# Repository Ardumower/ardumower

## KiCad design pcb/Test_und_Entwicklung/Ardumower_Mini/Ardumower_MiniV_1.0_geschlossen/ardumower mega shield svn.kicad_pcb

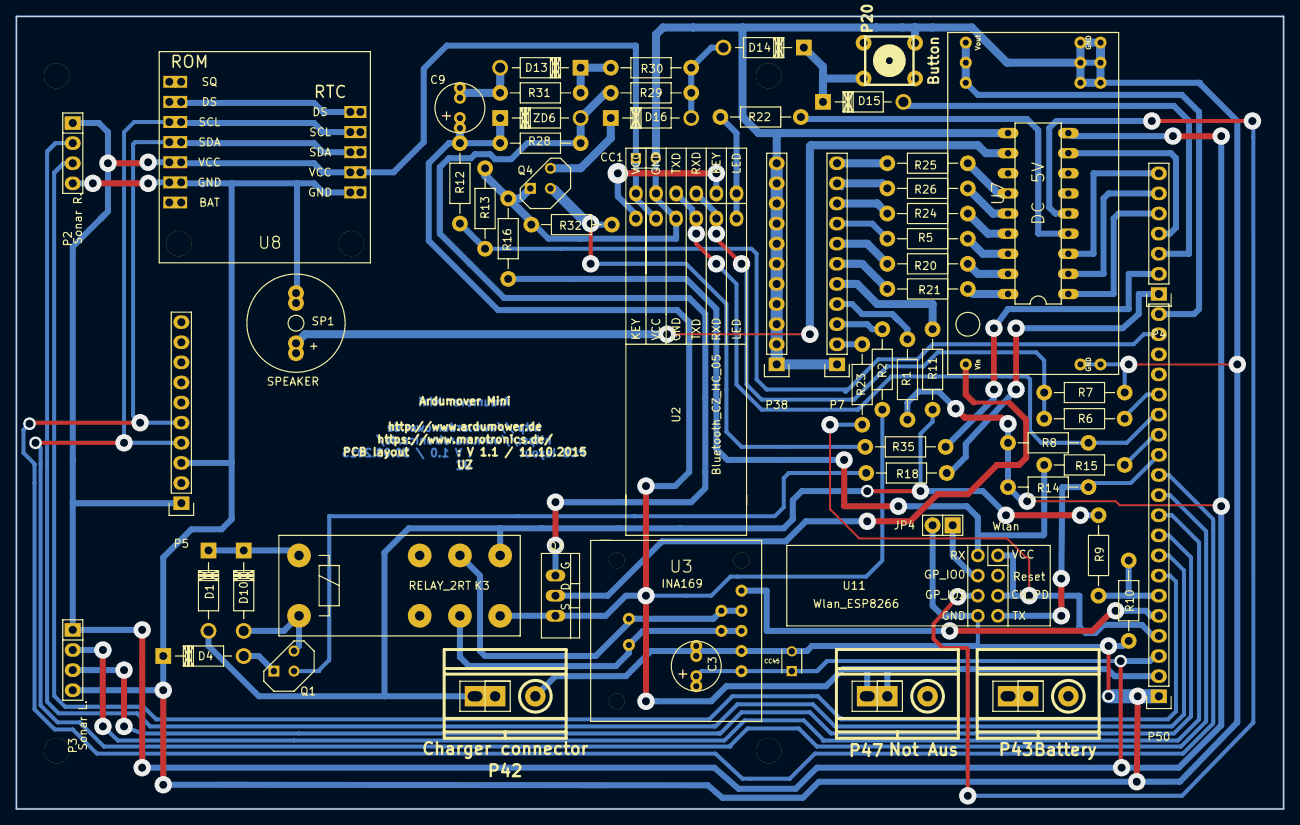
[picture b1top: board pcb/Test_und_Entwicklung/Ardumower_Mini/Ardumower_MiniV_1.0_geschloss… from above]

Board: 2 copper layers, 160.0 x 100.1 mm, 67 parts (0 on the bottom side), 64 nets.

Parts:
B1, B2, B3, B4: Bohrloch_3,2mm
C3: 1,0uF; Elko_vert_11.2x6.3mm_RM2.5_RM5.0
C9: 22uF; Elko_vert_11.2x6.3mm_RM2.5_RM5.0
CC1, CC45: 100nF; C_Disc_D3_P2.5
D1, D4, D10, D14, D15: 1N4148; Diode_ligend_RM10
D13, D16: 1N5819; Diode_ligend_RM10
IC1: UDN2981A; 40xx-DIL18
JP4: Wlan; Pin_Header_Straight_1x02
K3: RELAY_2RT; Relais_DPDT_Schrack-RT2_RM5mm_3D_Kontaktbelegung_geändert_F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
P2: Sonar R.; Pin_Header_Straight_1x04
P3: Sonar L.; Pin_Header_Straight_1x04
P4: CONN_01X07; Pin_Header_Straight_1x07
P5: IMU Compas; Pin_Header_Straight_1x10
P7: Status LEDs; Pin_Header_Straight_1x11
P20: Button; PCB_PUSH
P38: Status LEDs GND; Pin_Header_Straight_1x11
P42: Charger connector; Anschlussklemme_RM5,08-RM7,62
P43: Battery; Anschlussklemme_RM5,08-RM7,62
P47: Not Aus; Anschlussklemme_RM5,08-RM7,62
P50: CONN_01X20; Pin_Header_Straight_1x20
Q1: BC547; TO92-EBC
Q3: IRF9540N; TO-220_FET-GDS_Vertical
Q4: BC337; TO92-EBC
R1, R5, R20, R21, R24, R25, R26: 220; Resistor_Horizontal_RM10mm
R2, R11: 1K5; Resistor_Horizontal_RM10mm
R6: 470R; Resistor_Horizontal_RM10mm
R7, R8, R14, R16, R29: 1K; Resistor_Horizontal_RM10mm
R9, R12: 47K 0,1%; Resistor_Horizontal_RM10mm
R10, R13: 5,10K 0,1%; Resistor_Horizontal_RM10mm
R15: 470; Resistor_Horizontal_RM10mm
R18: 2k2; Resistor_Horizontal_RM10mm
R22: 120; Resistor_Horizontal_RM10mm
R23, R30: 100; Resistor_Horizontal_RM10mm
R28: 100K; Resistor_Horizontal_RM10mm
R31, R32: 10K; Resistor_Horizontal_RM10mm
R35: 30K; Resistor_Horizontal_RM10mm
SP1: SPEAKER; Buzzer_12x9.5RM7.6_RM5.0
U2: Bluetooth_CZ_HC_05; Bluetooth_Buchse_Platz
U3: INA169
U7: DC 5V; DC_DC_DSN2596_mit_Bohrloch_doppelte_Lochreihe
U8: DS1307+; Tiny_RTC_DS1307_geändert_mit_Bohrloch_4Lochreihen
U11: Wlan_ESP8266; Wlan_ESP8266_3D
ZD6: ZPD15; Diode_ligend_RM10

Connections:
+3V3: P50.4, R23.1, U11.CH_P, U11.VCC
+5V: C3.1, CC1.1, CC45.1, IC1.9, P2.1, P3.1, P5.1, P50.3, R1.1, R8.2, R14.2, U2.VCC, U3.1, U8.VCC
+BATT: C9.1, K3.1, P47.1, P50.2, Q3.S, R2.1, R12.1, R28.1, ZD6.2
/UnterSpannungsSchutz/Batterieausgang 24V: Q3.D, U7.3
DuoLED-Rot: IC1.2, P4.6
DuoLED_Grün: IC1.1, P4.5
GND: C3.2, CC1.2, CC45.2, D4.2, IC1.10, JP4.2, P2.4, P3.4, P5.3, P7.1, P20.2, P38.1, P38.2, P38.3, P38.4, P38.5, P38.6, P38.7, P38.8, P38.9, P38.10, P38.11, P42.2, P43.2, P50.1, Q4.E, R7.2, R10.2, R13.2, R16.2, R32.2, SP1.1, U2.GND, U3.2, U7.1, U7.4, U8.GND, U11.GND
Led-BT: IC1.4, R22.2
Led-Status: IC1.3, P4.7
Led-Wlan: IC1.5, U11.GP_2
Motorstrom: P50.20, U7.2
unnamed: C9.2, D13.1, R31.1
unnamed: D1.2, D10.2, K3.8
unnamed: D4.1, Q1.E
unnamed: D10.1, K3.9, Q1.C
unnamed: D13.2, R30.1, R31.2
unnamed: D14.1, D16.1, R29.1, R30.2
unnamed: D14.2, D15.2, P20.1
unnamed: D16.2, Q4.C
unnamed: IC1.11, SP1.2
unnamed: IC1.13, R25.1
unnamed: IC1.14, R26.1
unnamed: IC1.15, R24.1
unnamed: IC1.16, R5.1
unnamed: IC1.17, R20.1
unnamed: IC1.18, R21.1
unnamed: JP4.1, U11.GP_0
unnamed: K3.5, U3.5
unnamed: K3.12, U3.4
unnamed: P7.2, R23.2
unnamed: P7.3, R2.2
unnamed: P7.4, R1.2
unnamed: P7.5, R11.2
unnamed: P7.6, R21.2
unnamed: P7.7, R20.2
unnamed: P7.8, R5.2
unnamed: P7.9, R24.2
unnamed: P7.10, R26.2
unnamed: P7.11, R25.2
unnamed: P43.1, P47.2
unnamed: Q1.B, R18.2
unnamed: Q3.G, R28.2, R29.2, ZD6.1
unnamed: Q4.B, R32.1, R35.1
unnamed: R6.2, R7.1, U2.RXD
unnamed: R15.2, R16.1, U11.RX
unnamed: R22.1, U2.LED
RX1: P50.13, R14.1, U11.TX
RX2: P50.15, R8.1, U2.TXD
SCL1: P5.4, P50.11, U8.SCL
SDA2: P5.5, P50.12, U8.SDA
StationLed: D1.1, K3.16, P42.1, R9.1, R11.1
TX1: P50.14, R15.1
TX2: P50.16, R6.1
pinBatteryVoltage: P50.19, R12.2, R13.1
pinButton: D15.1, P4.3
pinBuzzer: IC1.8, P4.4
pinChargeCurrent: P50.5, U3.3
pinChargeVoltage: P50.6, R9.2, R10.1
pinChargingEnable: P4.1, R18.1
pinSonarLeftEcho: P3.3, P50.9
pinSonarLeftTrigger: P3.2, P50.10
pinSonarRightEcho: P2.3, P50.7
pinSonarRightTrigger: P2.2, P50.8
pinUndervoltageSwitch: P4.2, R35.2

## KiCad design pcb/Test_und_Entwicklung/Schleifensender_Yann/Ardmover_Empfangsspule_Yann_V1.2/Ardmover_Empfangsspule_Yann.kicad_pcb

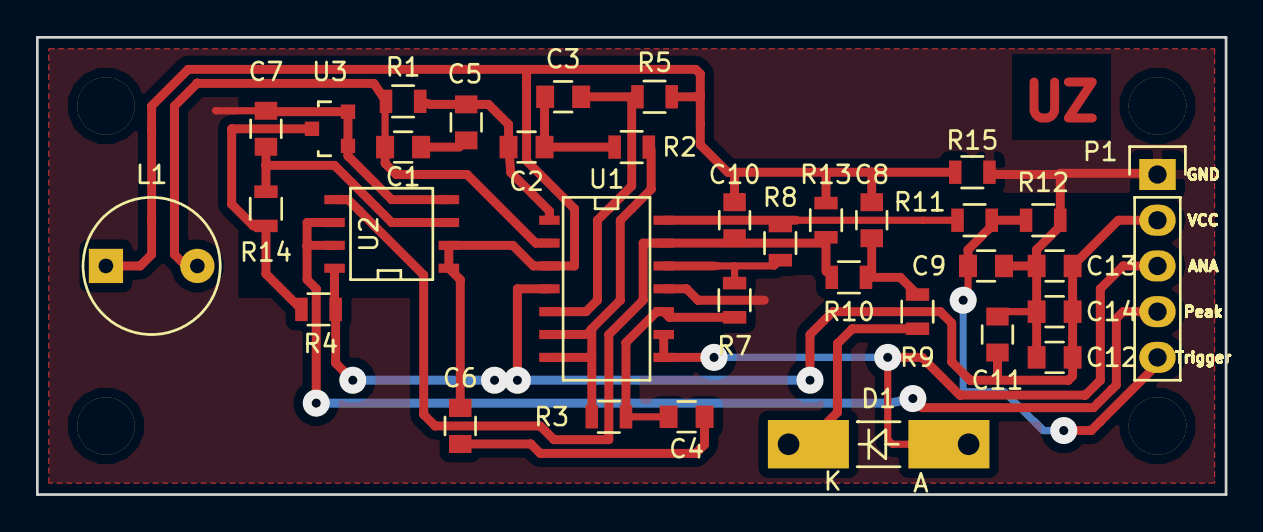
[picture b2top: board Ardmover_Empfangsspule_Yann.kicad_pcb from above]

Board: 2 copper layers, 66.0 x 25.4 mm, 38 parts (0 on the bottom side), 21 nets.

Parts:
B1, B2, B3, B4: Bohrloch; Bohrloch_3,2mm
C1, C4, C5, C6: 54pF; C_0805
C2, C3, C8, C9, C10: 10nF; C_0805
C7: 2,2uF; C_0805
C11, C13: 1uF; C_0805
C12, C14: 100nF; C_0805
D1: ZENER; MELF-RM10_Universal_Handsoldering
L1: 11P-154K-50; INDUCTOR_V
P1: CONN_01X05; Pin_Header_Straight_1x05
R1, R2, R3, R5, R7, R8, R9, R10, R11, R12, R13: 100K; R_0805
R4: 10K; R_0805
R14: 470; R_0805
R15: 470K; R_0805
U1: TLC274; SOIC-14_N
U2: TLC2272; SOIC-8-N
U3: LM 4040 AIM3-2,5; SOT-23

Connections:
ANA: D1.2, P1.3, U1.8, U1.9
GND: C7.2, C9.2, C11.2, C12.2, C13.2, C14.2, P1.1, R12.2, R15.2, U1.11, U2.4, U3.1, U3.2
GNDA: C6.2, C8.2, C10.2, L1.1, R5.2, R13.2, R15.1, U1.3, U2.1, U2.2
unnamed: C1.1, L1.2, R1.1, U1.2
unnamed: C1.2, C5.1
unnamed: C2.1, C5.2, R1.2, U1.1
unnamed: C2.2, C3.1, R2.1
unnamed: C3.2, R5.1, U1.5
unnamed: C4.1, R3.2, R7.1, U1.10
unnamed: C4.2, C6.1
unnamed: C7.1, R14.2, U2.3
unnamed: C8.1, R9.2, R10.1
unnamed: C10.1, R10.2, R13.1, U1.13, U2.5
unnamed: D1.1, R9.1
unnamed: R2.2, R3.1, U1.6, U1.7
unnamed: R7.2, R8.1, U1.12
unnamed: R8.2, R11.1, U1.14
unnamed: R4.2, R14.1, U3.3
Peak: P1.4, U2.6, U2.7
Trigger: C9.1, P1.5, R11.2, R12.1
VCC: C11.1, C12.1, C13.1, C14.1, P1.2, R4.1, U1.4, U2.8

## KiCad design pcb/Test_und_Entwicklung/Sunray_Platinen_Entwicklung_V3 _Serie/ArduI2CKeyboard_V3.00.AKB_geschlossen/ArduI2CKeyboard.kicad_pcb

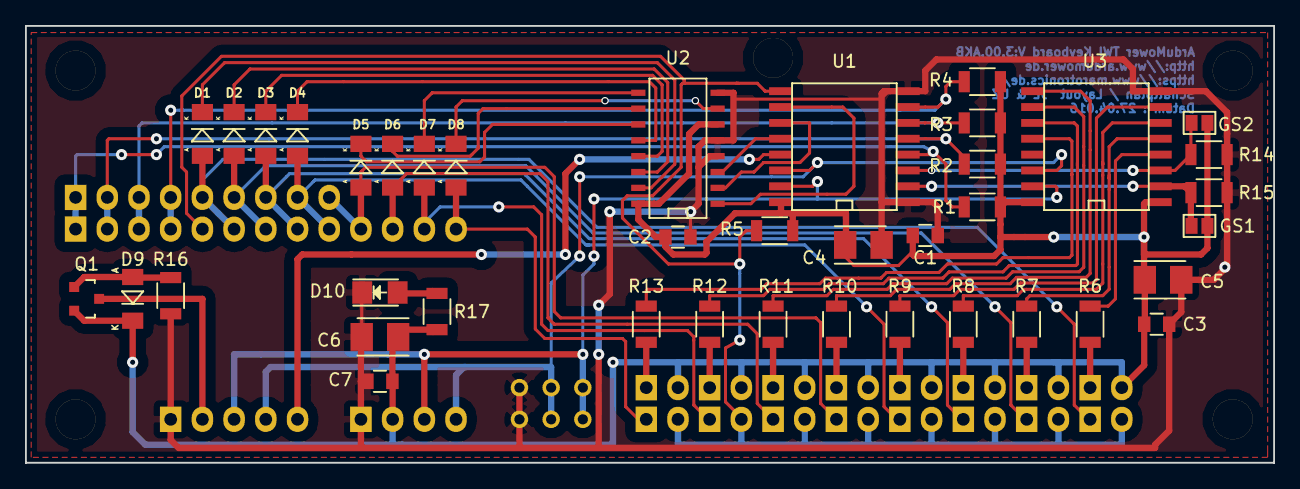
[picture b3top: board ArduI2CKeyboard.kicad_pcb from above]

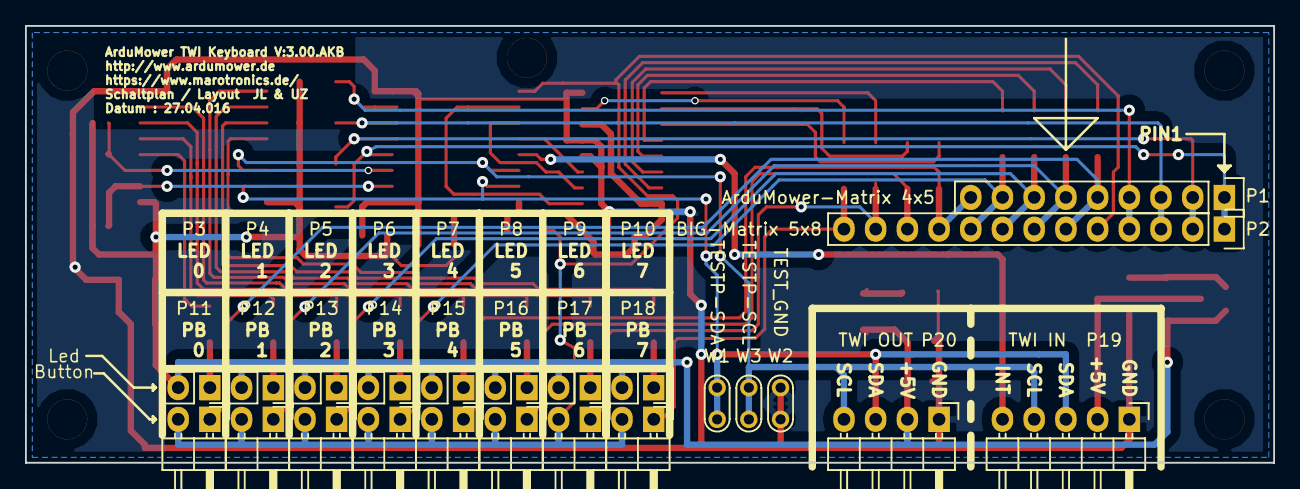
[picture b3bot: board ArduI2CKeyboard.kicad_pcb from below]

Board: 2 copper layers, 100.0 x 35.0 mm, 68 parts (23 on the bottom side), 50 nets.

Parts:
B1, B2, B3, B4, B5: Bohrloch_3,2mm
C1, C2, C3, C7: 100nF; C_0805
C4, C5, C6: 47µF 16V; TantalC_SizeB_EIA-3528_Reflow
D1, D2, D3, D4, D5, D6, D7, D8: LL4148; MiniMELF_Standard
D9: TZMC12; MiniMELF_Standard
D10: Power OK; LED_1206
GS1: A1; GS2
GS2: A2; GS2
P1: ArduMower-Matrix 4x5; Pin_Header_Straight_1x09
P2: BIG-Matrix 5x8; Pin_Header_Straight_1x13
P3: FUNCTION-LED 0; Pin_Header_Straight_1x02
P4: FUNCTION-LED 1; Pin_Header_Straight_1x02
P5: FUNCTION-LED 2; Pin_Header_Straight_1x02
P6: FUNCTION-LED 3; Pin_Header_Straight_1x02
P7: FUNCTION-LED 4; Pin_Header_Straight_1x02
P8: FUNCTION-LED 5; Pin_Header_Straight_1x02
P9: FUNCTION-LED 6; Pin_Header_Straight_1x02
P10: FUNCTION-LED 7; Pin_Header_Straight_1x02
P11: FUNCTION-PB 0; Pin_Header_Angled_1x02
P12: FUNCTION-PB 1; Pin_Header_Angled_1x02
P13: FUNCTION-PB 2; Pin_Header_Angled_1x02
P14: FUNCTION-PB 3; Pin_Header_Angled_1x02
P15: FUNCTION-PB 4; Pin_Header_Angled_1x02
P16: FUNCTION-PB 5; Pin_Header_Angled_1x02
P17: FUNCTION-PB 6; Pin_Header_Angled_1x02
P18: FUNCTION-PB 7; Pin_Header_Angled_1x02
P19: TWI IN; Pin_Header_Angled_1x05
P20: TWI OUT; Pin_Header_Angled_1x04
Q1: IRLML5203PBF; SOT-23
R1, R2, R3, R4, R5, R14, R15: 8K2; R_1206
R6, R7, R8, R9, R10, R11, R12, R13: 220; R_1206
R16: 10K; R_1206
R17: 1K; R_1206
U1, U3: PCF8574; SO-16-L
U2: 74LS138; SO-16-N
W1: TESTP-SDA; Test_Point
W2: TEST_GND; Test_Point
W3: TESTP-SCL; Test_Point

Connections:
+5V: C1.1, C2.1, C3.1, C4.1, C5.1, C6.1, C7.1, D9.1, GS1.2, GS2.2, P3.2, P4.2, P5.2, P6.2, P7.2, P8.2, P9.2, P10.2, P20.2, Q1.2, R1.2, R2.2, R3.2, R4.2, R5.2, R17.2, U1.16, U2.6, U2.16, U3.1, U3.16
GND: C1.2, C2.2, C3.2, C4.2, C5.2, C6.2, C7.2, D10.1, P19.1, P20.1, R14.1, R15.1, R16.2, U1.1, U1.8, U2.4, U2.5, U2.8, U3.8, W2.1
unnamed: D1.1, U2.15
unnamed: D1.2, P1.5, P2.6, P11.1
unnamed: D2.1, U2.14
unnamed: D2.2, P1.6, P2.7, P12.1
unnamed: D3.1, U2.13
unnamed: D3.2, P1.7, P2.8, P13.1
unnamed: D4.1, U2.12
unnamed: D4.2, P1.8, P2.9, P14.1
unnamed: D5.1, U2.11
unnamed: D5.2, P1.9, P2.10, P15.1
unnamed: D6.1, U2.10
unnamed: D6.2, P2.11, P16.1
unnamed: D7.1, U2.9
unnamed: D7.2, P2.12, P17.1
unnamed: D8.1, U2.7
unnamed: D8.2, P2.13, P18.1
unnamed: D9.2, Q1.1, R16.1
unnamed: D10.2, R17.1
unnamed: GS1.1, R15.2, U1.2, U3.2
unnamed: GS2.1, R14.2, U1.3, U3.3
unnamed: P1.1, P2.1, R1.1, U1.4
unnamed: P1.2, P2.2, R2.1, U1.5
unnamed: P1.3, P2.3, R3.1, U1.6
unnamed: P1.4, P2.4, R4.1, U1.7
unnamed: P3.1, R6.2
unnamed: P4.1, R7.2
unnamed: P5.1, R8.2
unnamed: P6.1, R9.2
unnamed: P7.1, R10.2
unnamed: P8.1, R11.2
unnamed: P9.1, R12.2
unnamed: P10.1, R13.2
unnamed: P2.5, P11.2, P12.2, P13.2, P14.2, P15.2, P16.2, P17.2, P18.2, R5.1, U1.9
unnamed: P19.2, Q1.3
unnamed: P19.3, P20.3, U1.15, U3.15, W1.1
unnamed: P19.4, P20.4, U1.14, U3.14, W3.1
unnamed: P19.5, U1.13
unnamed: R6.1, U3.4
unnamed: R7.1, U3.5
unnamed: R8.1, U3.6
unnamed: R9.1, U3.7
unnamed: R10.1, U3.9
unnamed: R11.1, U3.10
unnamed: R12.1, U3.11
unnamed: R13.1, U3.12
unnamed: U1.10, U2.1
unnamed: U1.11, U2.2
unnamed: U1.12, U2.3

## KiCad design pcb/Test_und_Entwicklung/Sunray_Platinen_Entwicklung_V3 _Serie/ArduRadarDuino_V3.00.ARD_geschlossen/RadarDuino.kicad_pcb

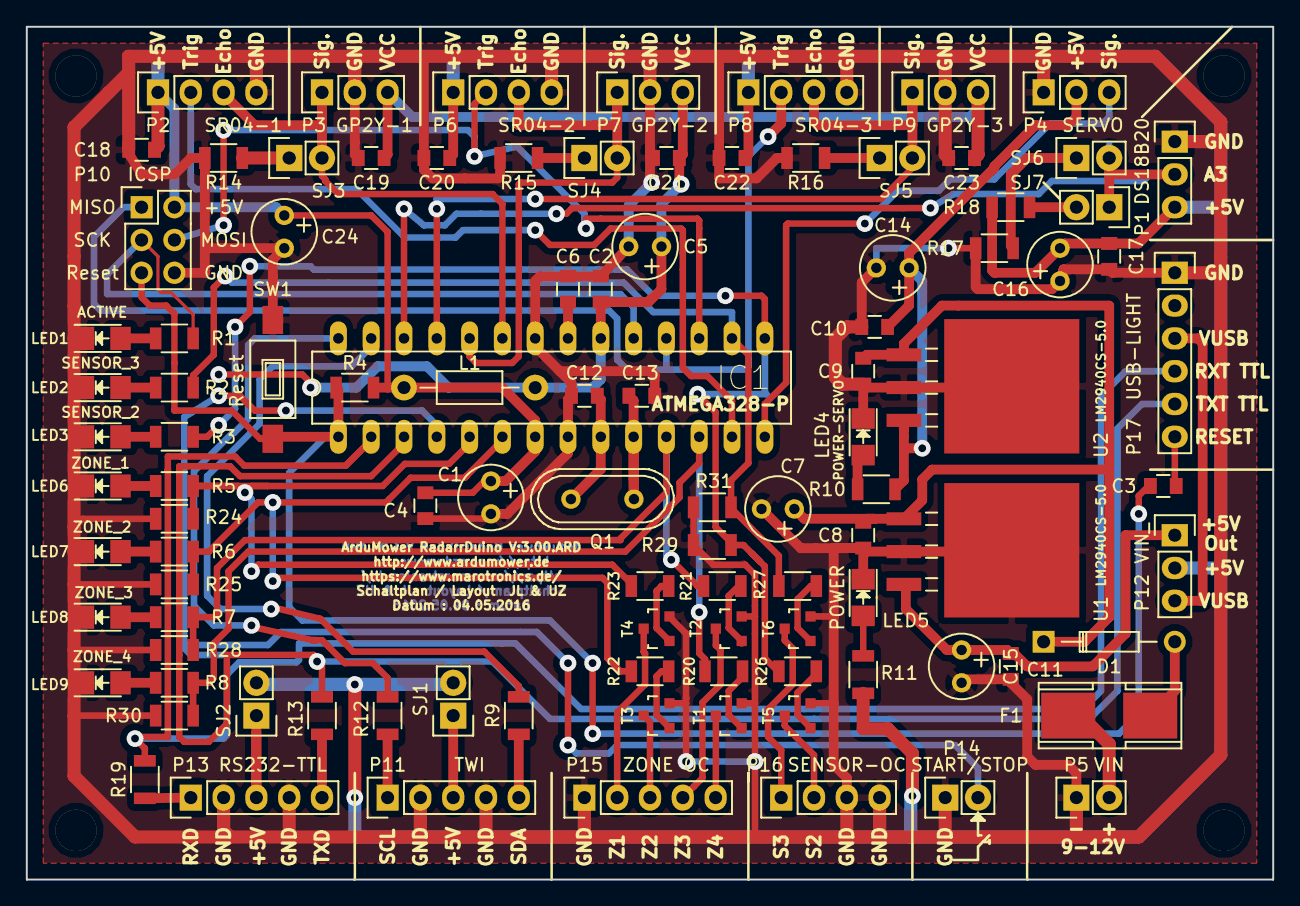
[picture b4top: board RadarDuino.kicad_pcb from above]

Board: 2 copper layers, 96.5 x 66.0 mm, 106 parts (0 on the bottom side), 66 nets.

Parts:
B1, B2, B3, B4: Bohrloch; Bohrloch_3,2mm
C1, C5, C16, C24: 10uF; Elko_vert_11x5mm_RM2.5
C2, C3, C4, C6, C8, C9, C10, C11, C17, C18, C19, C20, C21, C22, C23: 100nF; C_0805
C7, C14, C15: 22uF; Elko_vert_11x5mm_RM2.5
C12, C13: 27pF; C_0805
D1: 1N4004; Diode_DO-35_SOD27_Horizontal_RM10
F1: PTC; Fuse_SMD
IC1: ATMEGA328-P; atmega8-DIL28-3
L1: 10uH; Resistor_Horizontal_RM10mm
LED1: ACTIVE; LED_1206
LED2: SENSOR_3; LED_1206
LED3: SENSOR_2; LED_1206
LED4: POWER-SERVO; LED_1206
LED5: POWER; LED_1206
LED6: ZONE_1; LED_1206
LED7: ZONE_2; LED_1206
LED8: ZONE_3; LED_1206
LED9: ZONE_4; LED_1206
P1: DS18B20; Pin_Header_Straight_1x03
P2: SR04-1; Pin_Header_Straight_1x04
P3: GP2Y-1; Pin_Header_Straight_1x03
P4: SERVO; Pin_Header_Straight_1x03
P5: VIN; Pin_Header_Straight_1x02
P6: SR04-2; Pin_Header_Straight_1x04
P7: GP2Y-2; Pin_Header_Straight_1x03
P8: SR04-3; Pin_Header_Straight_1x04
P9: GP2Y-3; Pin_Header_Straight_1x03
P10: ICSP; Pin_Header_Straight_2x03
P11: TWI; Pin_Header_Straight_1x05
P12: VIN_; Pin_Header_Straight_1x03
P13: RS232-TTL; Pin_Header_Straight_1x05
P14: START/STOP; Pin_Header_Straight_1x02
P15: ZONE OC; Pin_Header_Straight_1x05
P16: SENSOR-OC; Pin_Header_Straight_1x04
P17: USB-LIGHT; Pin_Header_Straight_1x06
Q1: 16MHz; Crystal_HC49-U_Vertical
R1, R2, R3, R4, R5, R6, R7, R8, R10, R11: 1K; R_1206
R9, R12, R13, R19: 100; R_1206
R14, R15, R16, R17, R24, R25, R28, R29, R30, R31: 10K; R_1206
R18: 4K7; R_1206
R20, R21, R22, R23, R26, R27: 2K7; R_1206
SJ1, SJ2, SJ3, SJ4, SJ5, SJ6, SJ7: Jumper_NC_Small; Pin_Header_Straight_1x02
SW1: Reset; SW_SPST_FSMSM
T1, T2, T3, T4, T5, T6: BC847B; SOT-23
U1, U2: LM2940CS-5.0; TO254P1435X464-4N

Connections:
+5V: C1.1, C4.2, C16.2, C17.1, C18.1, C20.1, C22.1, C24.1, IC1.7, L1.1, P1.3, P2.1, P6.1, P8.1, P10.2, P12.2, R4.2, R11.1, R18.1, SJ1.2, SJ2.2
+5V-SERVO: C10.1, C14.1, P4.2, R10.1, U2.3
ADC0: IC1.23, P2.3, P3.1, SJ3.2
ADC1: IC1.24, P6.3, P7.1, SJ4.2
ADC2: IC1.25, P8.3, P9.1, SJ5.2
ADC3: IC1.26, P1.2, SJ6.2, SJ7.1
GND: C1.2, C2.2, C4.1, C5.2, C6.2, C7.2, C8.2, C9.2, C10.2, C11.2, C12.2, C13.2, C14.2, C15.2, C16.1, C17.2, C18.2, C19.1, C20.2, C21.1, C22.2, C23.1, C24.2, IC1.8, IC1.22, LED1.1, LED2.1, LED3.1, LED4.1, LED5.1, LED6.1, LED7.1, LED8.1, LED9.1, P1.1, P2.4, P3.2, P4.1, P5.1, P6.4, P7.2, P8.4, P9.2, P10.6, P11.2, P11.4, P13.2, P13.4, P14.1, P15.1, P16.3, P16.4, P17.1, R14.1, R15.1, R16.1, R17.1, R24.2, R25.2, R28.2, R29.2, R30.2, R31.2, SW1.2, T1.2, T2.2, T3.2, T4.2, T5.2, T6.2, U1.2, U1.4, U2.2, U2.4
MISO: IC1.18, P8.2, P10.1
MOSI: IC1.17, P6.2, P10.4
unnamed: C3.1, P17.6
unnamed: C6.1, IC1.21
unnamed: C7.1, C8.1, C9.1, D1.1, U1.1, U2.1
unnamed: C11.1, C15.1, P12.1, U1.3
unnamed: C12.1, IC1.9, Q1.2
unnamed: C13.1, IC1.10, Q1.1
unnamed: D1.2, F1.2
unnamed: F1.1, P5.2
unnamed: LED1.2, R1.1
unnamed: LED2.2, R2.1
unnamed: LED3.2, R3.1
unnamed: LED4.2, R10.2
unnamed: LED5.2, R11.2
unnamed: LED6.2, R5.1
unnamed: LED7.2, R6.1
unnamed: LED8.2, R7.1
unnamed: LED9.2, R8.1
unnamed: P11.1, R12.2
unnamed: P11.3, SJ1.1
unnamed: P11.5, R9.2
unnamed: P13.1, R19.2
unnamed: P13.3, SJ2.1
unnamed: P13.5, R13.2
unnamed: P15.2, T4.3
unnamed: P15.3, T3.3
unnamed: P15.4, T2.3
unnamed: P15.5, T1.3
unnamed: P16.1, T6.3
unnamed: P16.2, T5.3
unnamed: R14.2, SJ3.1
unnamed: R15.2, SJ4.1
unnamed: R16.2, SJ5.1
unnamed: R17.2, SJ6.1
unnamed: R18.2, SJ7.2
unnamed: R20.1, T1.1
unnamed: R21.1, T2.1
unnamed: R22.1, T3.1
unnamed: R23.1, T4.1
unnamed: R26.1, T5.1
unnamed: R27.1, T6.1
RXD_TTL: IC1.2, P17.4, R19.1
Reset: C3.2, IC1.1, P10.5, R4.1, SW1.1
SCK: IC1.19, P10.3, R1.2
SCL: IC1.28, R12.1
SDA: IC1.27, R9.1
SENSOR-2: IC1.15, R3.2, R26.2, R29.1
SENSOR-3: IC1.16, R2.2, R27.2, R31.1
SERVO: IC1.14, P4.3
START-STOP: IC1.4, P14.2
TRIG: IC1.13, P2.2
TXD_TTL: IC1.3, P17.5, R13.1
VCC: C2.1, C5.1, C19.2, C21.2, C23.2, IC1.20, L1.2, P3.3, P7.3, P9.3
VUSB: P12.3, P17.3
ZONE-1: IC1.5, R5.2, R23.2, R24.1
ZONE-2: IC1.6, R6.2, R22.2, R25.1
ZONE-3: IC1.11, R7.2, R21.2, R28.1
ZONE-4: IC1.12, R8.2, R20.2, R30.1

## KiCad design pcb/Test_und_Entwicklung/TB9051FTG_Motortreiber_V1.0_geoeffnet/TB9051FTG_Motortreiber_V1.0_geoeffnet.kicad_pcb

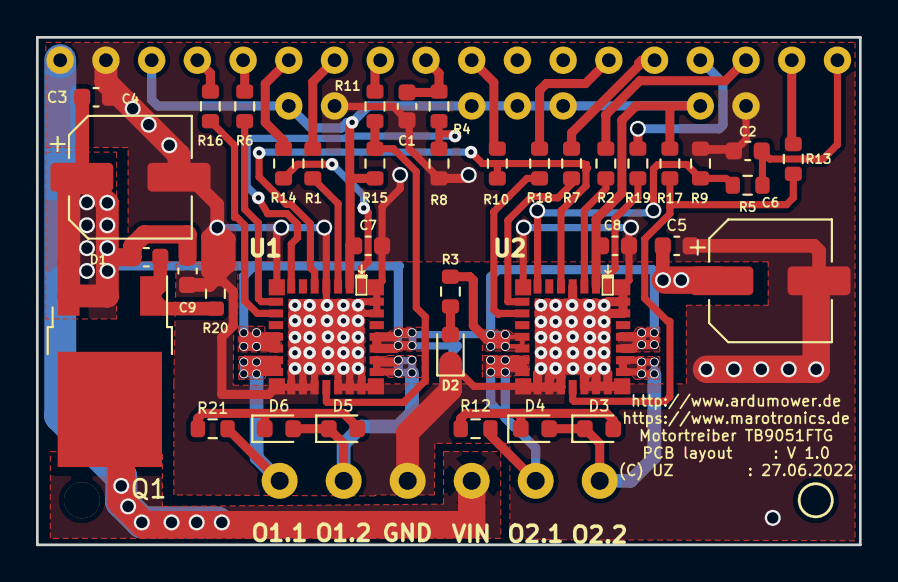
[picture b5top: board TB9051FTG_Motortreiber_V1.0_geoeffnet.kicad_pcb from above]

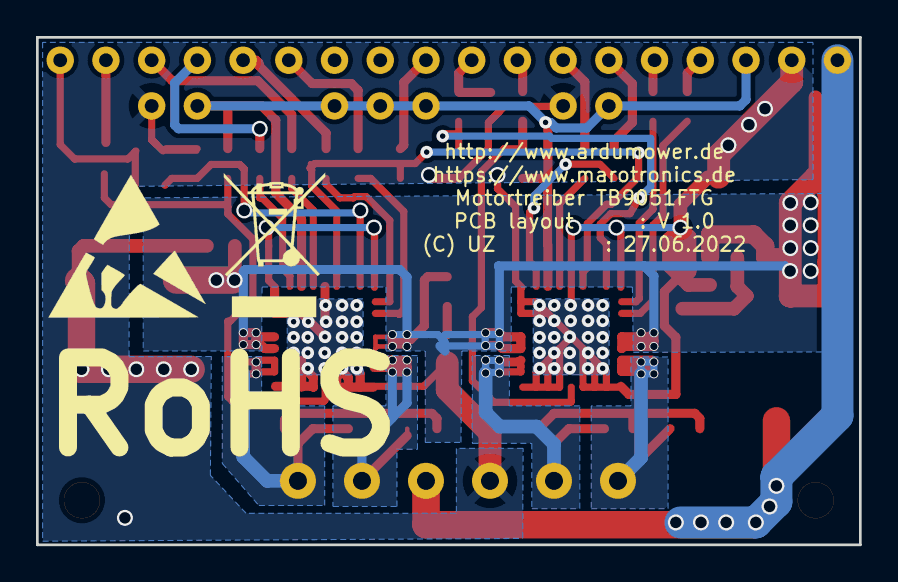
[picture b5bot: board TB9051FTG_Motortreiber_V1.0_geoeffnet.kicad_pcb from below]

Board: 2 copper layers, 45.7 x 28.2 mm, 42 parts (2 on the bottom side), 38 nets.

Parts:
C1, C2: 470nF 25V; C_0603_1608Metric
C3, C5, C7, C8, C9: 100nF 50V; C_0603_1608Metric
C4, C6: 47uF 50V; CP_Elec_6.3x5.8
D1: ZENER 16.2V; C_0603_1608Metric
D2: LED_Blau; LED_0603_1608Metric
D3, D5: LED_Rot; LED_0603_1608Metric
D4, D6: LED_Grün; LED_0603_1608Metric
H1: WEEE-Logo; WEEE-Logo_5.6x8mm_SilkScreen
H2: ESD-Logo; ESD-Logo_8.9x8mm_SilkScreen
Q1: D4185; TO-252-2
R1, R2, R4, R5, R6, R7, R10, R14, R16, R18, R19: 1k; R_0603_1608Metric
R3, R12, R21: 4.7k; R_0603_1608Metric
R8, R9, R11, R13: 220; R_0603_1608Metric
R15, R17: 10k; R_0603_1608Metric
R20: 100k; R_0603_1608Metric
U1, U2: TB9051FTG
U3: Motortreiber TB9051FTG; mc33926_breakout_footprint

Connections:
EN: R10.2, U1.5 (EN), U2.5 (EN)
GND: C1.2, C2.2, C3.2, C4.2, C5.2, C6.2, C7.1, C8.1, C9.1, D2.1 (K), R8.2, R9.2, R20.1, U1.4 (AGND), U1.15 (PGND_1), U1.16 (PGND_2), U1.17 (PGND_3), U1.19 (PGND_4), U1.20 (PGND_5), U1.21 (PGND_6), U1.27 (TEST1), U1.28 (TEST2), U1.29 (EP), U1.C1 (CORNER1), U1.C2 (CORNER2), U1.C3 (CORNER3), U1.C4 (CORNER4), U2.4 (AGND), U2.15 (PGND_1), U2.16 (PGND_2), U2.17 (PGND_3), U2.19 (PGND_4), U2.20 (PGND_5), U2.21 (PGND_6), U2.27 (TEST1), U2.28 (TEST2), U2.29 (EP), U2.C1 (CORNER1), U2.C2 (CORNER2), U2.C3 (CORNER3), U2.C4 (CORNER4), U3.2 (GND), U3.21 (GND)
IORF: C7.2, C8.2, R15.2, R17.2, U1.2 (VCC), U2.2 (VCC), U3.3 (Vdd)
M1D1-7->U1-ENB-3: R1.2, U1.3 (ENB)
M1FB-9->U1-OCM-7: C1.1, R4.1, U3.9 (M1FB)
M1IN1-5->U1-PWM1-8: R6.2, U1.8 (PWM1)
M1IN2-4->U1-PWM2-9: R16.2, U1.9 (PWM2)
M1OUT1: R21.1, U1.13 (OUT1_1), U1.14 (OUT1_2), U3.19 (M1OUT1)
M1OUT2: D5.1 (K), D6.2 (A), U1.22 (OUT2_1), U1.23 (OUT2_2), U3.20 (M1OUT2)
M1nD2-6->U1-OCC-1: R14.2, U1.1 (OCC)
M1nSF-8->U1-DIAG-18: R11.1, U3.8 (M1nSF)
M2D1-16->U2-ENB-3: R2.2, U2.3 (ENB)
M2IN1-14->U2-PWM1-8: R7.2, U2.8 (PWM1)
M2IN2-13->U2-PWM2-9: R18.2, U2.9 (PWM2)
M2OUT1: R12.1, U2.13 (OUT1_1), U2.14 (OUT1_2), U3.23 (M2OUT1)
M2OUT2: D3.1 (K), D4.2 (A), U2.22 (OUT2_1), U2.23 (OUT2_2), U3.24 (M2OUT2)
M2_FB-18->U2-OCM-7: C2.1, R5.1, U3.18 (M2_FB)
M2nD2-15->U2-OCC-1: R19.2, U2.1 (OCC)
M2nSF-17->U2-DIAG-18: R13.1, U3.17 (M2nSF)
unnamed: D1.1 (A), Q1.1 (G), R20.2
unnamed: D2.2 (A), R3.2
unnamed: D3.2 (A), D4.1 (K), R12.2
unnamed: D5.2 (A), D6.1 (K), R21.2
unnamed: R11.2, R15.1, U1.18 (DIAG)
unnamed: R4.2, R8.1, U1.7 (OCM)
unnamed: R13.2, R17.1, U2.18 (DIAG)
unnamed: R5.2, R9.1, U2.7 (OCM)
unnamed: R10.1, U3.10 (EN)
unnamed: R1.1, U3.7 (M1D1)
unnamed: R6.1, U3.5 (M1IN1)
unnamed: R16.1, U3.4 (M1IN2)
unnamed: R14.1, U3.6 (M1nD2)
unnamed: R2.1, U3.16 (M2D1)
unnamed: R7.1, U3.14 (M2IN1)
unnamed: R18.1, U3.13 (M2IN2)
unnamed: R19.1, U3.15 (M2nD2)
VIN: Q1.2 (D), U3.1 (VIN), U3.22 (VIN)
VOUT: C3.1, C4.1, C5.1, C6.1, C9.2, D1.2 (K), Q1.3 (S), R3.1, U1.11 (VBAT_1), U1.12 (VBAT_2), U1.24 (VBAT_3), U1.25 (VBAT_4), U2.11 (VBAT_1), U2.12 (VBAT_2), U2.24 (VBAT_3), U2.25 (VBAT_4)
